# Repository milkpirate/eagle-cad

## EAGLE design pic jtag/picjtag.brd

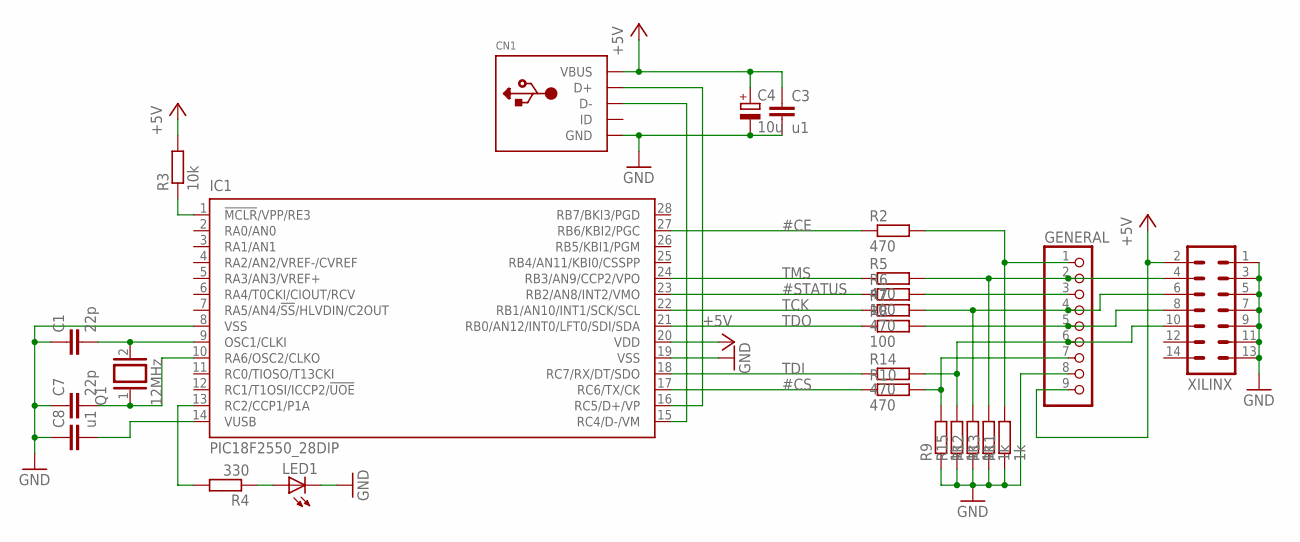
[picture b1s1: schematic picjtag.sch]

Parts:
C1, C7: 22p; C025-025X050
C3, C8: u1; C025-025X050
C4: 10u; E2,5-6E
CN1: USBTHM; USB-MINIB-THM
GENERAL: PINHD-1X9; 1X09
IC1: PIC18F2550_28DIP; DIL28-3
LED1: LED3MM
Q1: 12MHz; QS
R2, R5, R7, R10, R14: 470; 0207/2V
R3: 10k; 0207/2V
R4: 330; 0207/2V
R6, R8: 100; 0207/2V
R9, R11, R12, R13, R15: 1k; 0207/2V
XILINX: ML14

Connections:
#CE: IC1.27 (RB6/KBI2/PGC), R2.1
#CS: IC1.17 (RC6/TX/CK), R10.1
#STATUS: IC1.23 (RB2/AN8/INT2/VMO), R6.1
+5V: C3.1, C4.+, CN1.VBUS, GENERAL.9, IC1.20 (VDD), R3.2, XILINX.2
GND: C1.1, C3.2, C4.-, C7.1, C8.1, CN1.GND, GENERAL.8, IC1.8 (VSS), IC1.19 (VSS), LED1.K (C), R9.1, R11.1, R12.1, R13.1, R15.1, XILINX.1, XILINX.3, XILINX.5, XILINX.7, XILINX.9, XILINX.11, XILINX.13
unnamed: C7.2, IC1.10 (RA6/OSC2/CLKO), Q1.1
unnamed: IC1.1 (!MCLR!/VPP/RE3), R3.1
unnamed: CN1.D-, IC1.15 (RC4/D-/VM)
unnamed: CN1.D+, IC1.16 (RC5/D+/VP)
unnamed: IC1.13 (RC2/CCP1/P1A), R4.2
unnamed: LED1.A, R4.1
unnamed: C1.2, IC1.9 (OSC1/CLKI), Q1.2
unnamed: C8.2, IC1.14 (VUSB)
unnamed: GENERAL.7, R9.2, R10.2
unnamed: GENERAL.6, R14.2, R15.2, XILINX.10
unnamed: GENERAL.4, R7.2, R12.2, XILINX.6
unnamed: GENERAL.2, R5.2, R13.2, XILINX.4
unnamed: GENERAL.1, R2.2, R11.2
unnamed: GENERAL.5, R8.2, XILINX.8
unnamed: GENERAL.3, R6.2
TCK: IC1.22 (RB1/AN10/INT1/SCK/SCL), R7.1
TDI: IC1.18 (RC7/RX/DT/SDO), R14.1
TDO: IC1.21 (RB0/AN12/INT0/LFT0/SDI/SDA), R8.1
TMS: IC1.24 (RB3/AN9/CCP2/VPO), R5.1

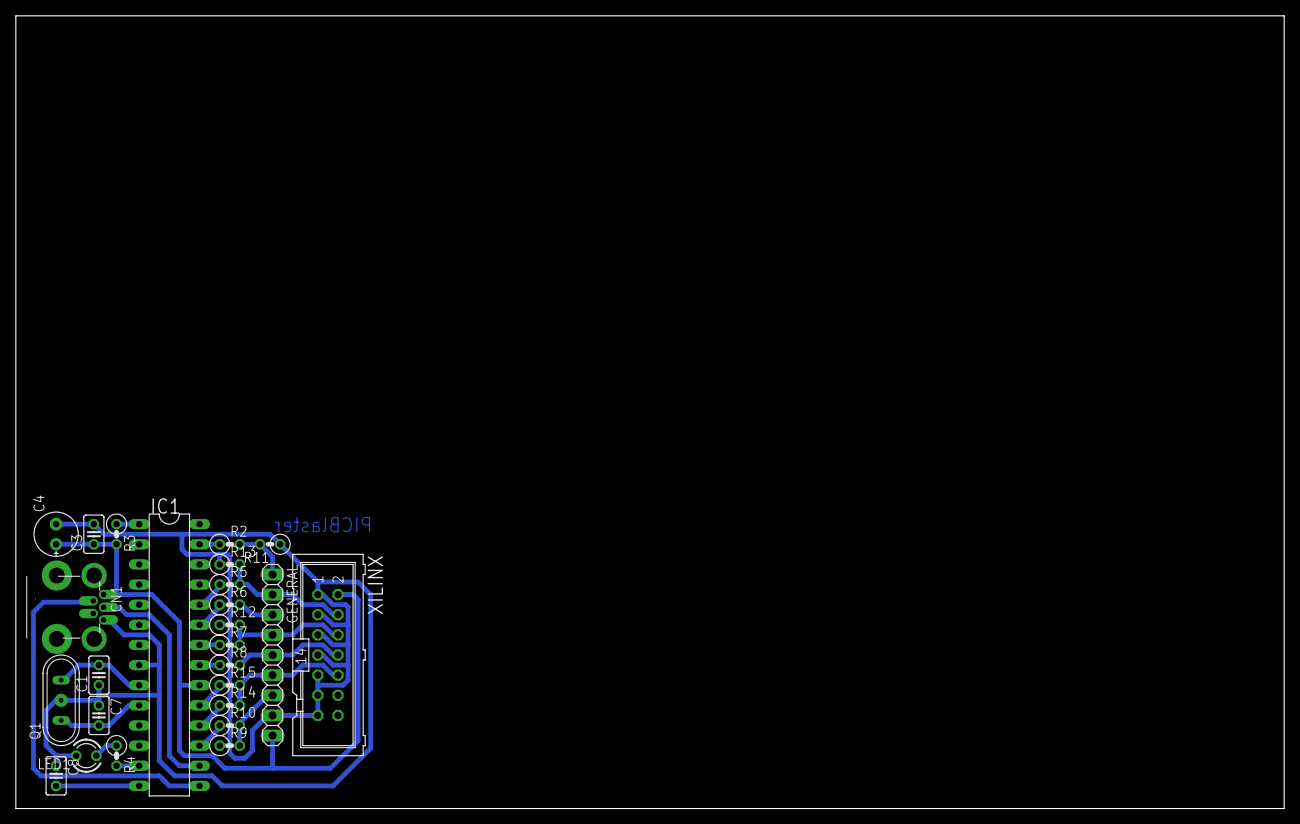
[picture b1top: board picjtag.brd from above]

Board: 2 copper layers, 160.0 x 100.0 mm, 25 parts (0 on the bottom side), 24 nets.

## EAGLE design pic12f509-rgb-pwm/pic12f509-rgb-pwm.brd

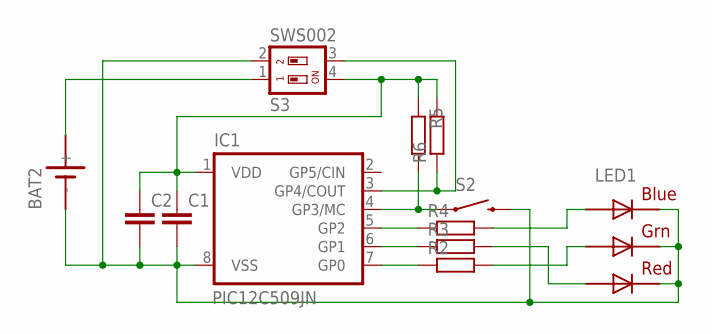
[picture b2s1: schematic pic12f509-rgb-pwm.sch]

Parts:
BAT2: SN2032
C1, C2: C-EUC0805K; C0805K
IC1: PIC12C509JN; DIL8
LED1: RGBLED5050
R2, R3, R4, R5, R6: R-EU_M0805; M0805
S2: SWITCH-MOMENTARY-2-SMD-1101NE; TACTILE-SWITCH-1101NE
S3: SWS002; SMS-002

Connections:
GND: BAT2.-, C1.2, C2.2, IC1.8 (VSS), LED1.4 (BLUE_C), LED1.5 (RED_C), LED1.6 (GREEN_C), S2.2, S3.2
unnamed: C1.1, C2.1, IC1.1 (VDD), R5.1, R6.2, S3.4
unnamed: LED1.1 (GREEN_A), R2.2
unnamed: BAT2.+, S3.1
unnamed: IC1.4 (GP3/MC), R5.2, S2.1
unnamed: LED1.2 (RED_A), R3.2
unnamed: IC1.7 (GP0), R2.1
unnamed: IC1.6 (GP1), R3.1
unnamed: IC1.5 (GP2), R4.1
unnamed: LED1.3 (BLUE_A), R4.2
unnamed: IC1.3 (GP4/COUT), R6.1, S3.3

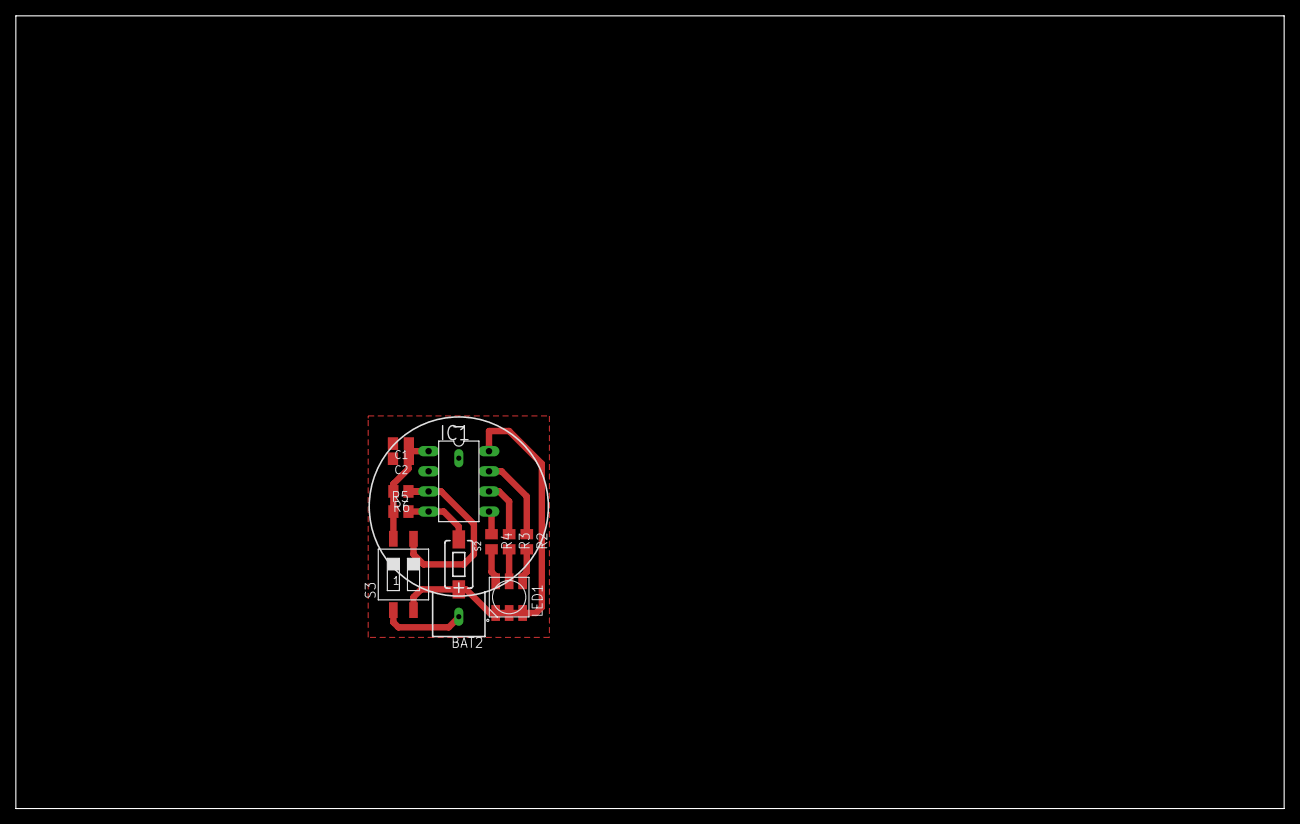
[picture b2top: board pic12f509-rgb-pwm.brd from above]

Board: 2 copper layers, 160.0 x 100.0 mm, 12 parts (0 on the bottom side), 11 nets.

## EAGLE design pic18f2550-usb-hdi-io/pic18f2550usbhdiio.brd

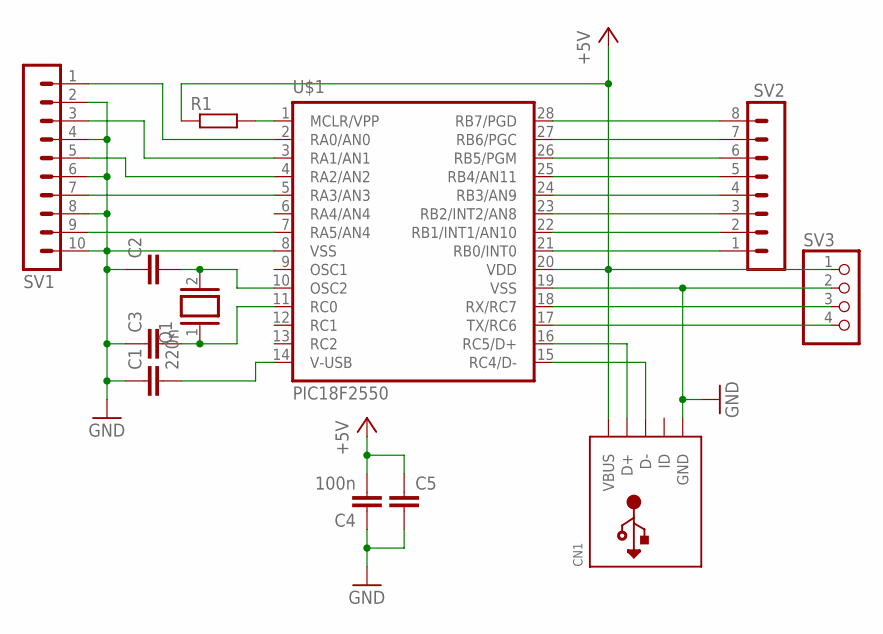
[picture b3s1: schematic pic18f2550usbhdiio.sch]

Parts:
C1: 220n; C025-025X050
C2, C3: C-EU025-025X050; C025-025X050
C4: 100n; C025-025X050
C5: C-EUC0805K; C0805K
CN1: USBMOLEX; USB-MINIB-THM-MOLEX
Q1: XTAL/S; QS
R1: R-EU_0207/10; 0207/10
SV1: MA10-1
SV2: MA08-1
SV3: PINHD-1X4; 1X04
U$1: PIC18F2550; DIL28-3

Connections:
+5V: C4.2, C5.1, CN1.VBUS, R1.1, SV3.1, U$1.20 (VDD)
D+: CN1.D+, U$1.16 (RC5/D+)
D-: CN1.D-, U$1.15 (RC4/D-)
GND: C1.1, C2.1, C3.1, C4.1, C5.2, CN1.GND, SV1.2, SV1.4, SV1.6, SV1.8, SV1.10, SV3.2, U$1.8 (VSS), U$1.19 (VSS)
unnamed: SV1.1, U$1.2 (RA0/AN0)
unnamed: SV1.3, U$1.3 (RA1/AN1)
unnamed: SV1.5, U$1.4 (RA2/AN2)
unnamed: SV1.7, U$1.5 (RA3/AN3)
unnamed: SV1.9, U$1.7 (RA5/AN4)
unnamed: SV3.3, U$1.18 (RX/RC7)
unnamed: SV2.1, U$1.21 (RB0/INT0)
unnamed: SV2.2, U$1.22 (RB1/INT1/AN10)
unnamed: SV2.3, U$1.23 (RB2/INT2/AN8)
unnamed: SV2.4, U$1.24 (RB3/AN9)
unnamed: SV2.5, U$1.25 (RB4/AN11)
unnamed: SV2.6, U$1.26 (RB5/PGM)
unnamed: SV2.7, U$1.27 (RB6/PGC)
unnamed: SV2.8, U$1.28 (RB7/PGD)
unnamed: C3.2, Q1.1, U$1.11 (RC0)
unnamed: C2.2, Q1.2, U$1.10 (OSC2)
unnamed: C1.2, U$1.14 (V-USB)
unnamed: SV3.4, U$1.17 (TX/RC6)
unnamed: R1.2, U$1.1 (MCLR/VPP)

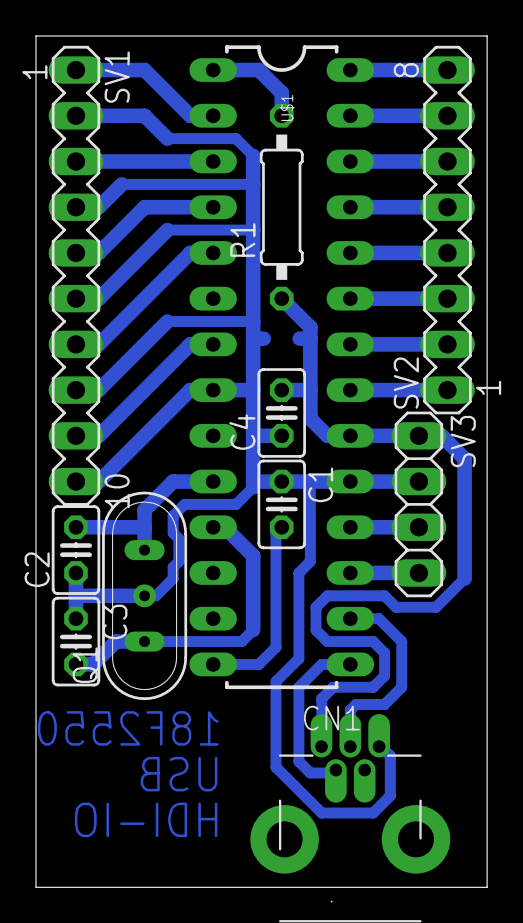
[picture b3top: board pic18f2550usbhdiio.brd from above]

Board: 2 copper layers, 25.1 x 47.3 mm, 12 parts (1 on the bottom side), 23 nets.

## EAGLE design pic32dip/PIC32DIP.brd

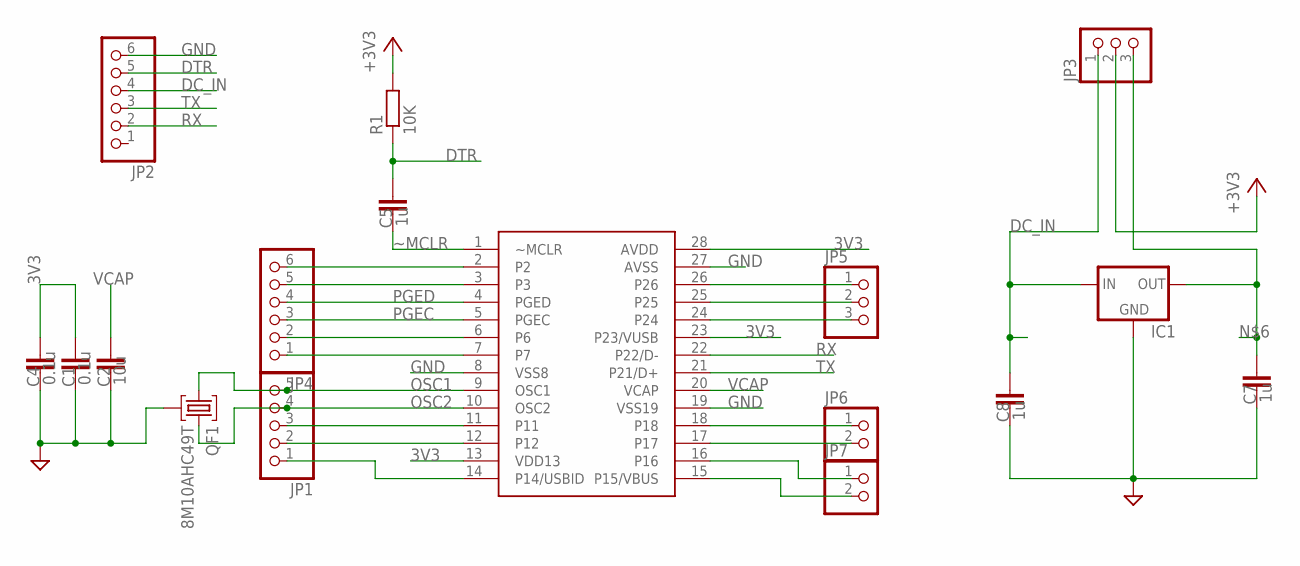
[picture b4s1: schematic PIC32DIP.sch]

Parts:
C1, C4: 0.1u; C805
C2: 10u; C805
C5, C8: 1u; C805
C7: 1u; C1206
IC1: MCP1700_SOT-89-ROUND; SOT89
JP1: PINHD-1X5; 1X05
JP2: PINHD-1X6/90; 1X06/90
JP3, JP5: PINHD-1X3; 1X03
JP4: PINHD-1X6; 1X06
JP6, JP7: PINHD-1X2; 1X02
QF1: 8M10AHC49T; HC49U
R1: 10K; 0204/7
U$1: PIC32DIP; SOCKET-28-3

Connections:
3V3: C1.1, C4.1, JP3.2, R1.2, U$1.13 (VDD13), U$1.23 (P23/VUSB), U$1.28 (AVDD)
DC_IN: C8.1, IC1.2 (IN), IC1.4 (IN), JP2.4, JP3.1
DTR: C5.1, JP2.5, R1.1
GND: C1.2, C2.2, C4.2, C7.2, C8.2, IC1.1 (GND), JP2.6, QF1.2, U$1.8 (VSS8), U$1.19 (VSS19), U$1.27 (AVSS)
unnamed: JP4.6, U$1.2
unnamed: JP4.5, U$1.3
unnamed: JP4.2, U$1.6
unnamed: JP4.1, U$1.7
unnamed: JP1.3, U$1.11
unnamed: C7.1, IC1.3 (OUT), JP3.3
unnamed: JP1.2, U$1.12
unnamed: JP1.1, U$1.14 (P14/USBID)
unnamed: JP7.1, U$1.16
unnamed: JP6.2, U$1.17
unnamed: JP6.1, U$1.18
unnamed: JP5.1, U$1.26
unnamed: JP5.2, U$1.25
unnamed: JP5.3, U$1.24
OSC1: JP1.5, QF1.1, U$1.9 (OSC1)
OSC2: JP1.4, QF1.3, U$1.10 (OSC2)
PGEC: JP4.3, U$1.5 (PGEC)
PGED: JP4.4, U$1.4 (PGED)
RX: JP2.2, U$1.22 (P22/D-)
TX: JP2.3, U$1.21 (P21/D+)
VBUS: JP7.2, U$1.15 (P15/VBUS)
VCAP: C2.1, U$1.20 (VCAP)
~MCLR: C5.2, U$1.1 (~MCLR)

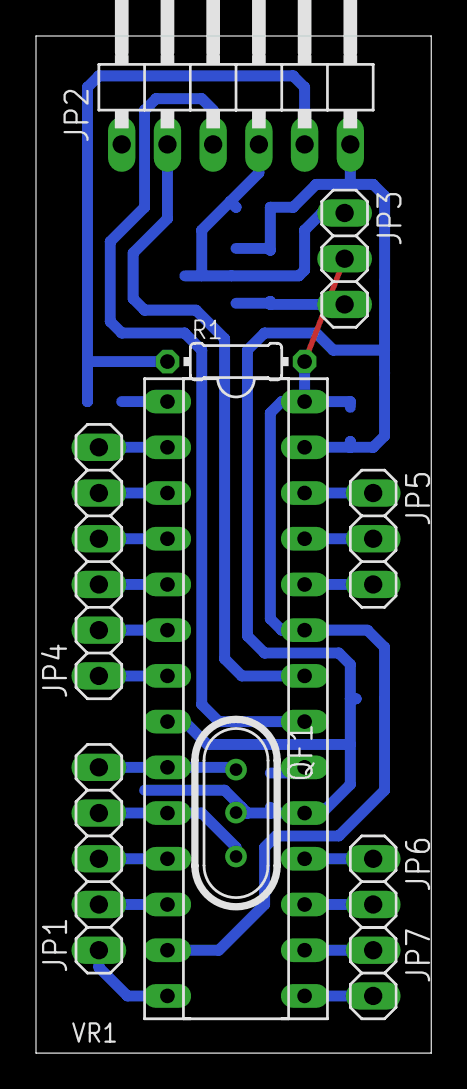
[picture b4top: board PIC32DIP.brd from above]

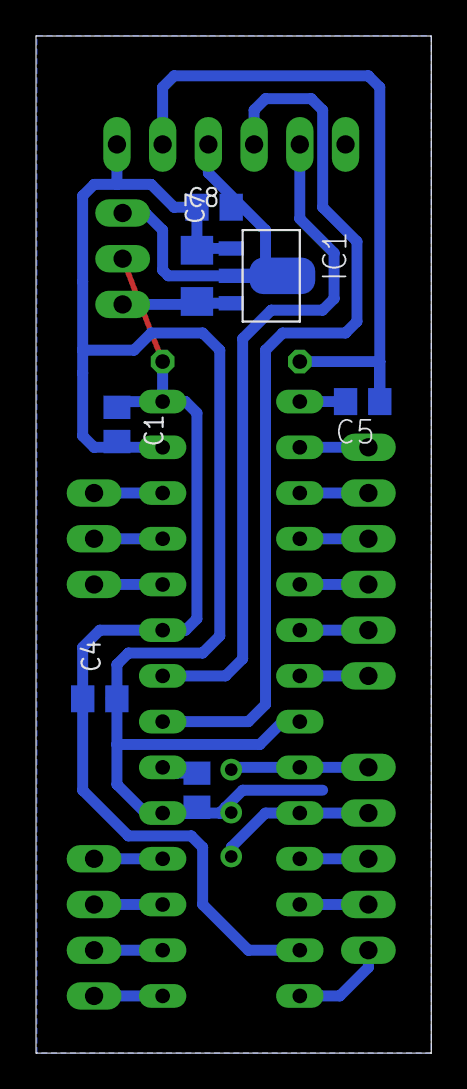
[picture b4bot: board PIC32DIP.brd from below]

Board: 2 copper layers, 22.0 x 56.5 mm, 17 parts (7 on the bottom side), 27 nets.

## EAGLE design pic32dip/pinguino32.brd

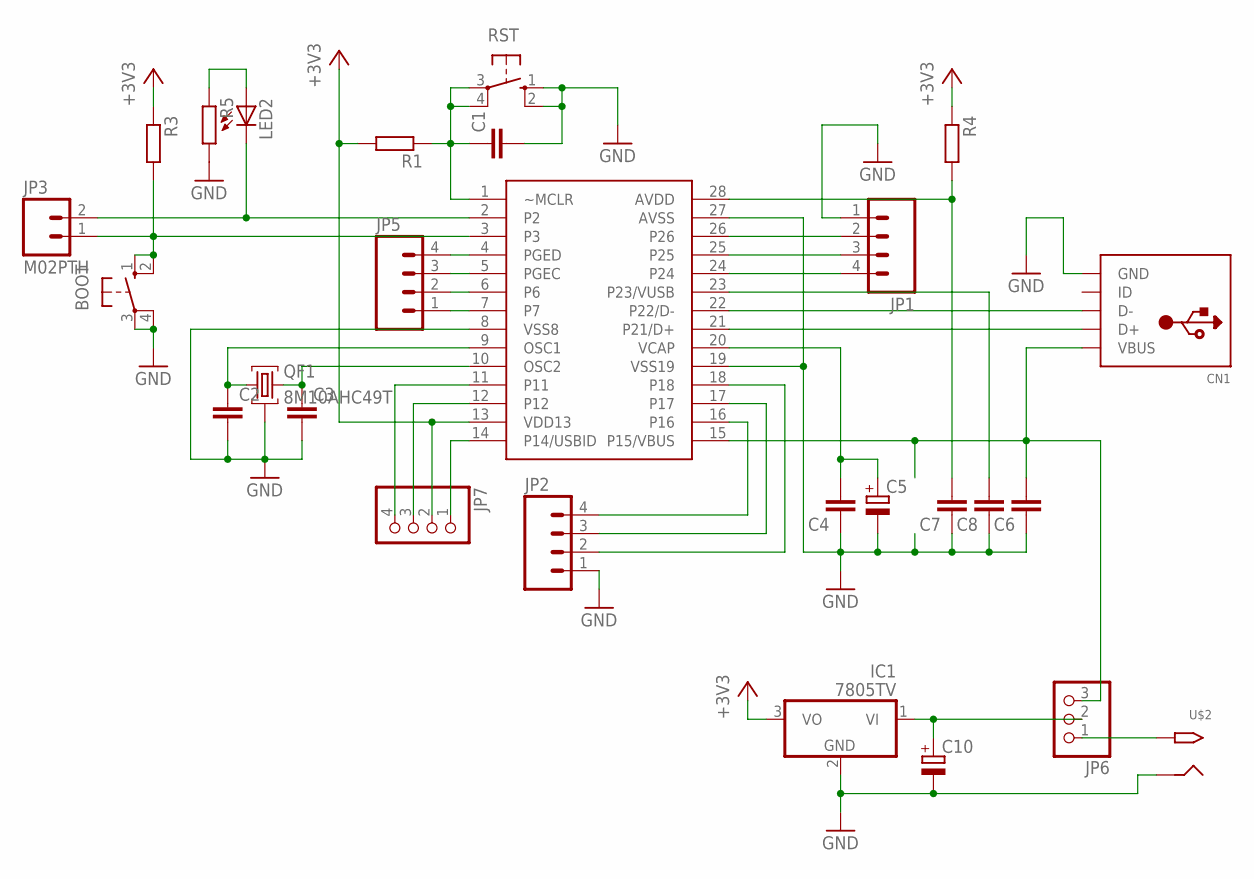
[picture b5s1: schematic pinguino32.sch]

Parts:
BOOT: 10-XX; B3F-10XX
C1, C2, C3, C4, C6, C7, C8: C-EU025-025X050; C025-025X050
C5, C10: CPOL-EUE2,5-6E; E2,5-6E
CN1: USBTHM; USB-MINIB-THM
IC1: 7805TV; TO220V
JP1, JP2, JP5: M04PTH; 1X04
JP3: M02PTH; 1X02
JP6: PINHD-1X3; 1X03
JP7: PINHD-1X4; 1X04
LED2: LED3MM
QF1: 8M10AHC49T; HC49U
R1, R4, R5: R-EU_0204/7; 0204/7
R3: R-EU_0204/2V; 0204V
RST: 10-XX; B3F-10XX
U$1: PIC32DIP; SOCKET-28-3
U$2: 2.1MMJACKTHM; PJ-102A

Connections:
+3V3: IC1.3 (VO), JP7.2, R1.2, R3.1, R4.1, U$1.13 (VDD13)
GND: BOOT.3, BOOT.4 (P1), C1.2, C2.2, C3.2, C4.1, C5.-, C6.1, C7.1, C8.1, C10.-, CN1.GND, IC1.2 (GND), JP1.1, JP2.1, QF1.2, R5.2, RST.1 (S), RST.2 (S1), U$1.8 (VSS8), U$1.19 (VSS19), U$1.27 (AVSS), U$2.RING
unnamed: C1.1, R1.1, RST.3, RST.4 (P1), U$1.1 (~MCLR)
unnamed: JP3.2, LED2.K (C), U$1.2
unnamed: LED2.A, R5.1
unnamed: JP5.1, U$1.7
unnamed: JP5.2, U$1.6
unnamed: JP5.3, U$1.5 (PGEC)
unnamed: JP5.4, U$1.4 (PGED)
unnamed: BOOT.1 (S), BOOT.2 (S1), JP3.1, R3.2, U$1.3
unnamed: C6.2, CN1.VBUS, JP6.3, U$1.15 (P15/VBUS)
unnamed: C7.2, R4.2, U$1.28 (AVDD)
unnamed: JP7.1, U$1.14 (P14/USBID)
unnamed: JP7.3, U$1.12
unnamed: JP7.4, U$1.11
unnamed: JP2.4, U$1.16
unnamed: JP2.3, U$1.17
unnamed: JP2.2, U$1.18
unnamed: JP6.1, U$2.TIP
unnamed: CN1.D-, U$1.22 (P22/D-)
unnamed: CN1.D+, U$1.21 (P21/D+)
unnamed: C4.2, C5.+, U$1.20 (VCAP)
unnamed: C10.+, IC1.1 (VI), JP6.2
unnamed: C8.2, U$1.23 (P23/VUSB)
unnamed: JP1.2, U$1.26
unnamed: JP1.3, U$1.25
unnamed: JP1.4, U$1.24
unnamed: C3.1, QF1.3, U$1.10 (OSC2)
unnamed: C2.1, QF1.1, U$1.9 (OSC1)

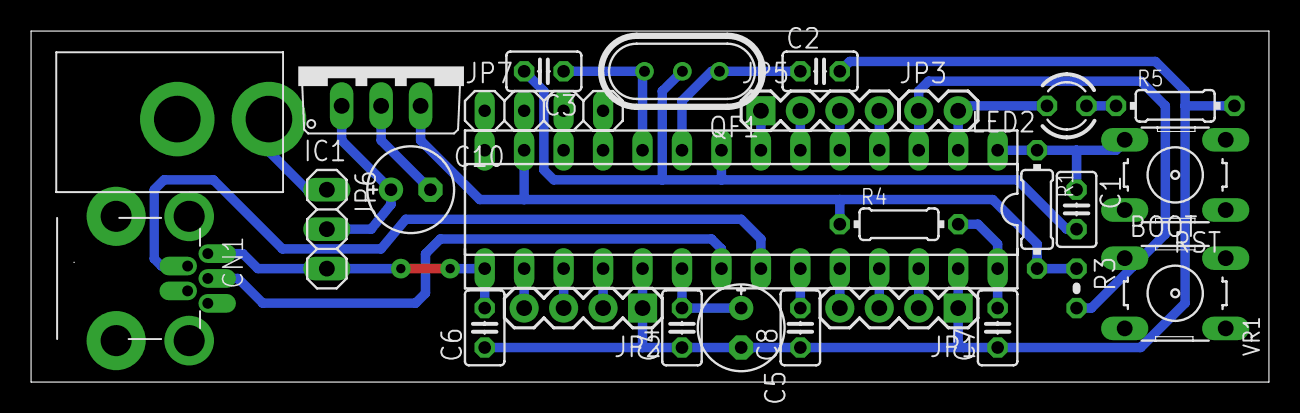
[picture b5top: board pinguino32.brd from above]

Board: 2 copper layers, 79.7 x 22.6 mm, 27 parts (0 on the bottom side), 29 nets.

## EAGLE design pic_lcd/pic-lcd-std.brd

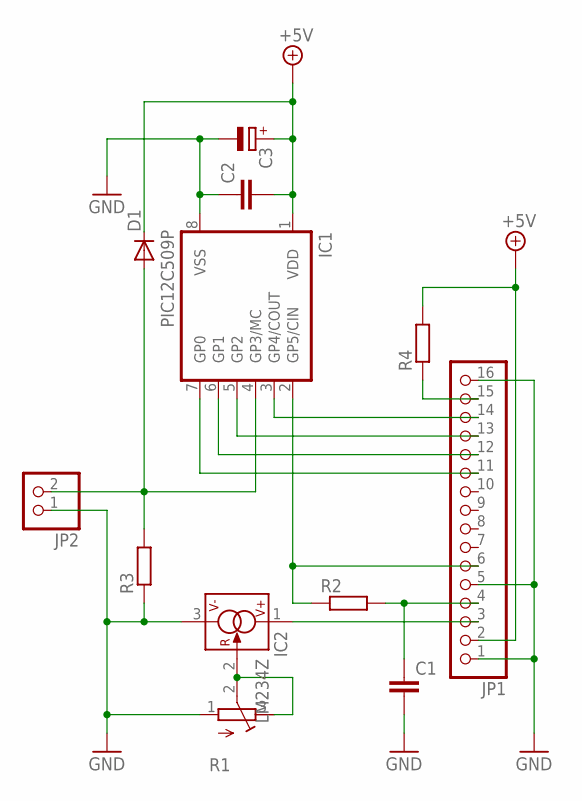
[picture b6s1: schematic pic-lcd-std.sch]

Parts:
C1, C2: C-EU025-025X050; C025-025X050
C3: CPOL-EUTT2D5L; TT2D5L
D1: DIODE-DO34-7; DO34-7
IC1: PIC12C509P; DIL8
IC2: LM234Z; TO92
JP1: PINHD-1X16; 1X16
JP2: PINHD-1X2/90; 1X02/90
R1: R-TRIMM3296P; RTRIM3296P
R2, R3, R4: R-EU_0204/7; 0204/7

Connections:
+5V: C2.2, C3.+, D1.C, IC1.1 (VDD), JP1.2, R4.2
GND: C1.2, C2.1, C3.-, IC1.8 (VSS), IC2.3 (V-), JP1.1, JP1.5, JP1.16, JP2.1, R1.1 (A), R3.1
unnamed: IC2.1 (V+), JP1.3
unnamed: C1.1, JP1.4, R2.2
unnamed: D1.A, IC1.4 (GP3/MC), JP2.2, R3.2
unnamed: IC1.2 (GP5/CIN), JP1.6, R2.1
unnamed: IC2.2 (R), R1.2 (S), R1.3 (E)
unnamed: IC1.7 (GP0), JP1.11
unnamed: IC1.6 (GP1), JP1.12
unnamed: IC1.5 (GP2), JP1.13
unnamed: IC1.3 (GP4/COUT), JP1.14
unnamed: JP1.15, R4.1

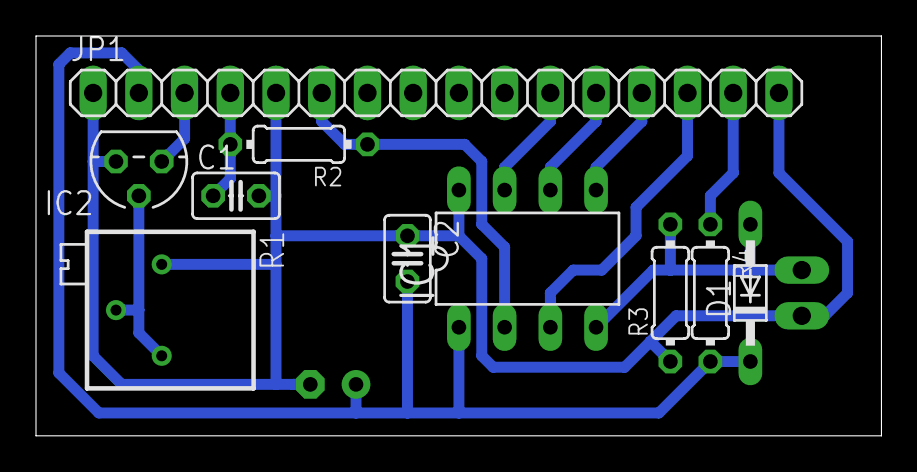
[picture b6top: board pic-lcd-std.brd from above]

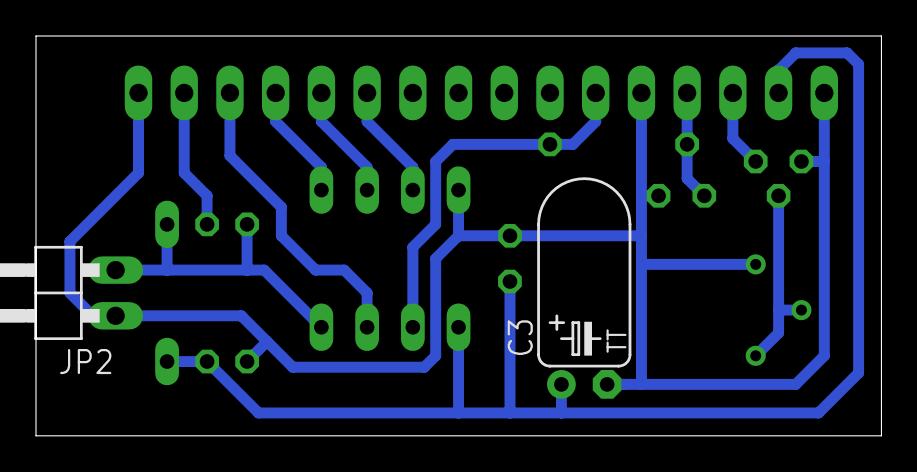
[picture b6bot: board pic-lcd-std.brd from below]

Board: 2 copper layers, 47.0 x 22.2 mm, 12 parts (2 on the bottom side), 12 nets.

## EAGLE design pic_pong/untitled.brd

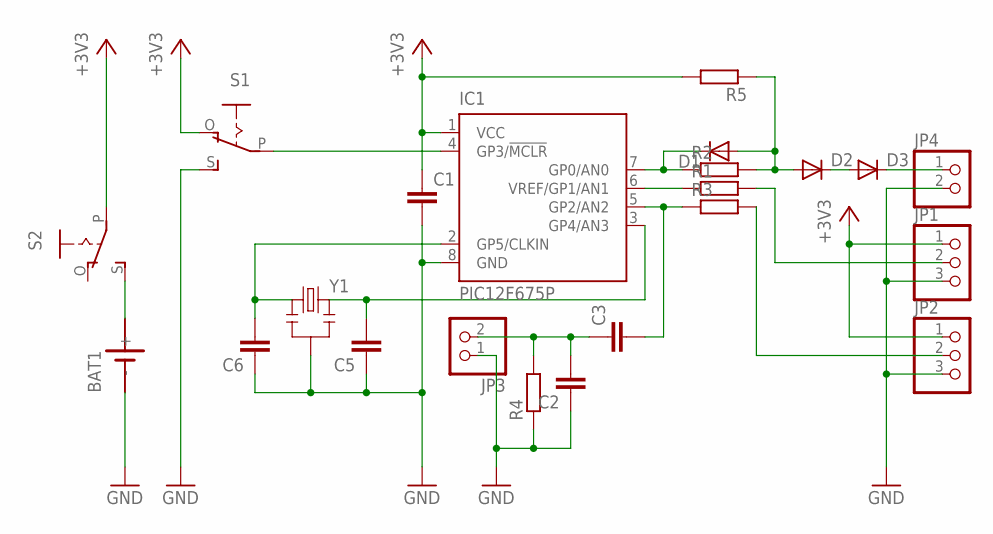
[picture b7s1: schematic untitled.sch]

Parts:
BAT1: SN2032
C1, C2, C3, C5, C6: C-EU025-025X050; C025-025X050
D1, D2, D3: DIODE-D-2.5; D-2.5
IC1: PIC12F675P; DIL8
JP1, JP2: PINHD-1X3; 1X03
JP3, JP4: PINHD-1X2; 1X02
R1, R2, R3, R4, R5: R-EU_0204/2V; 0204V
S1, S2: EG1218S; EG1218
Y1: RESONATORPTH; RESONATOR-PTH

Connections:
+3V3: C1.1, IC1.1 (VCC), JP1.1, JP2.1, R5.2, S1.O, S2.P
GND: BAT1.-, C1.2, C2.1, C5.1, C6.1, IC1.8 (GND), JP1.3, JP2.3, JP3.1, JP4.2, R4.1, S1.S, Y1.2
unnamed: C3.2, IC1.5 (GP2/AN2), R3.1
unnamed: IC1.6 (VREF/GP1/AN1), R1.1
unnamed: D1.C, IC1.7 (GP0/AN0), R2.1
unnamed: C2.2, C3.1, JP3.2, R4.2
unnamed: D3.C, JP4.1
unnamed: D2.C, D3.A
unnamed: D1.A, D2.A, R2.2, R5.1
unnamed: C6.2, IC1.2 (GP5/CLKIN), Y1.1
unnamed: JP2.2, R3.2
unnamed: IC1.4 (GP3/!MCLR), S1.P
unnamed: C5.2, IC1.3 (GP4/AN3), Y1.3
unnamed: JP1.2, R1.2
unnamed: BAT1.+, S2.S

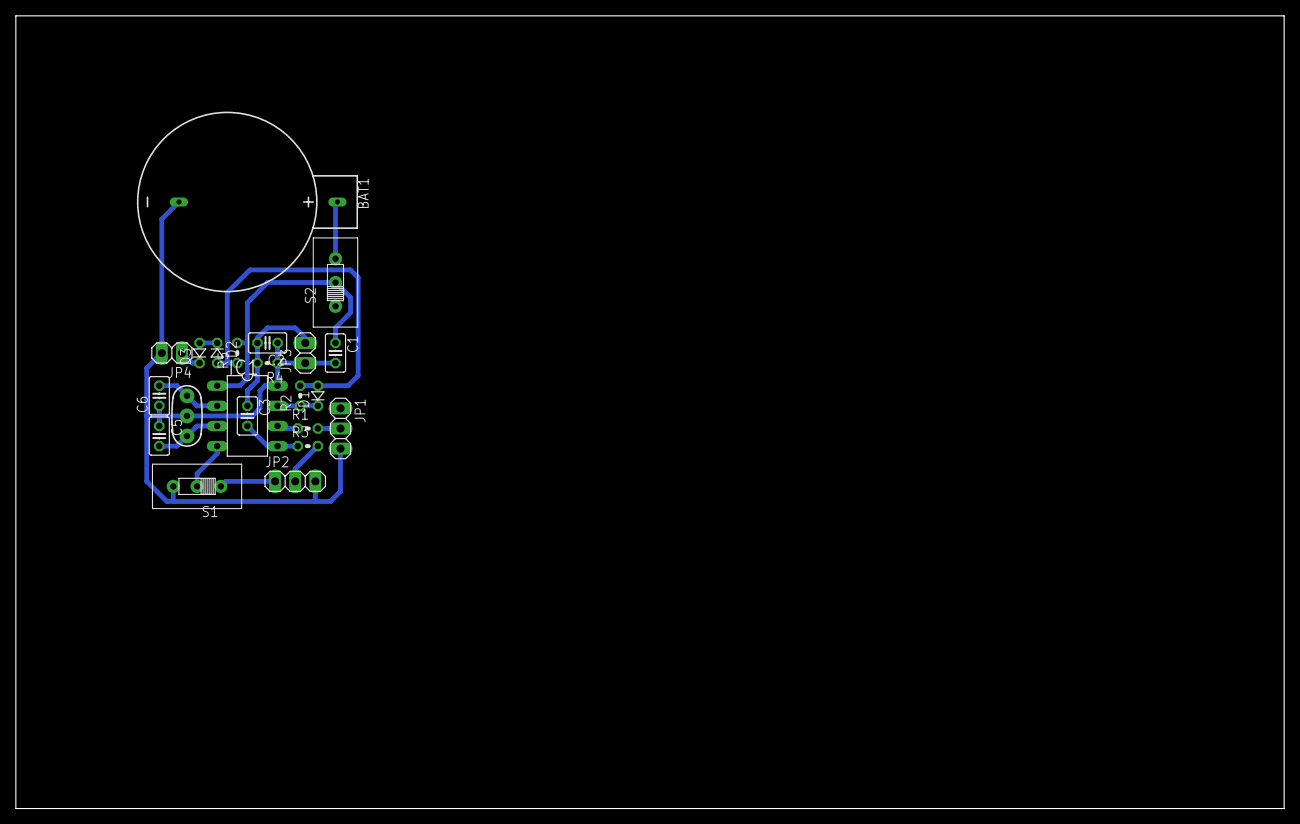
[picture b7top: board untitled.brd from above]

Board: 2 copper layers, 160.0 x 100.0 mm, 22 parts (0 on the bottom side), 15 nets.

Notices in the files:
parts and their libraries:
SparkFun-Electromechanical: Licensing: Creative Commons ShareAlike 4.0 International - https://creativecommons.org/licenses/by-sa/4.0
SparkFun: Licensing: CC v3.0 Share-Alike You are welcome to use this library for commercial purposes.
